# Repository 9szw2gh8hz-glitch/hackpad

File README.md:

<H1>Quel's Micropad

A small, customizable 5-key macropad with a rotary encoder, powered by the Seeed Studio XIAO RP2040-DIP.
Designed for simple shortcuts and macros.

<H1>Screenshots

<H1>BOM
  
1. Seeed XIAO RP2040-DIP
2. 5 Cherry MX Mechanical Switches
3. 5 1N4148 Diodes
4. EC11 Rotary Encoder
5. 4 M3x16mm screws

<H1>Firmware
This macropad can run two firmwares:

- QMK
- KMK

<H1>Assembly

1. Solder diodes
2. Solder MX switches
3. Insert and solder the XIAO RP2040-DIP
4. Solder the rotary encoder
5. Attach switches + keycaps
6. crew the case together
7. Flash firmware (QMK/KMK)

<H1>Usage

Use it for streaming macros, Photoshop tools, coding shortcuts, volume knob, or gaming functions
Encoder can control volume, scrolling, timeline scrubbing, etc.

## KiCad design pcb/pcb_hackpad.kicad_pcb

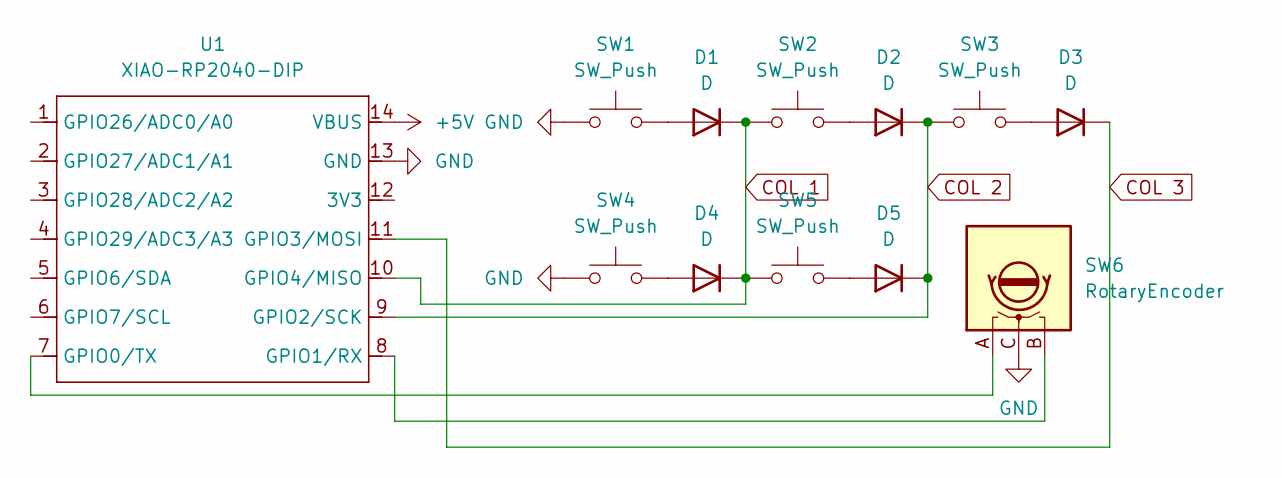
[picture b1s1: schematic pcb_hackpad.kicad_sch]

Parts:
D1, D2, D3, D4, D5: D; LED_PLCC-2_3.4x3.0mm_AK
SW1, SW2, SW3, SW4, SW5: SW_Push; SW_Cherry_MX_1.00u_PCB
SW6: RotaryEncoder; RotaryEncoder_Alps_EC11E_Vertical_H20mm_CircularMountingHol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
U1: XIAO-RP2040-DIP

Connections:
+5V: U1.14 (VBUS)
COL 1: D1.1 (K), D4.1 (K), SW2.1, SW5.1, U1.10 (GPIO4/MISO)
COL 2: D2.1 (K), D5.1 (K), SW3.1, U1.9 (GPIO2/SCK)
COL 3: D3.1 (K), U1.11 (GPIO3/MOSI)
GND: SW1.1, SW4.1, SW6.C, U1.13 (GND)
unnamed: D1.2 (A), SW1.2
unnamed: D2.2 (A), SW2.2
unnamed: D3.2 (A), SW3.2
unnamed: D4.2 (A), SW4.2
unnamed: D5.2 (A), SW5.2
unnamed: SW6.A, U1.7 (GPIO0/TX)
unnamed: SW6.B, U1.8 (GPIO1/RX)

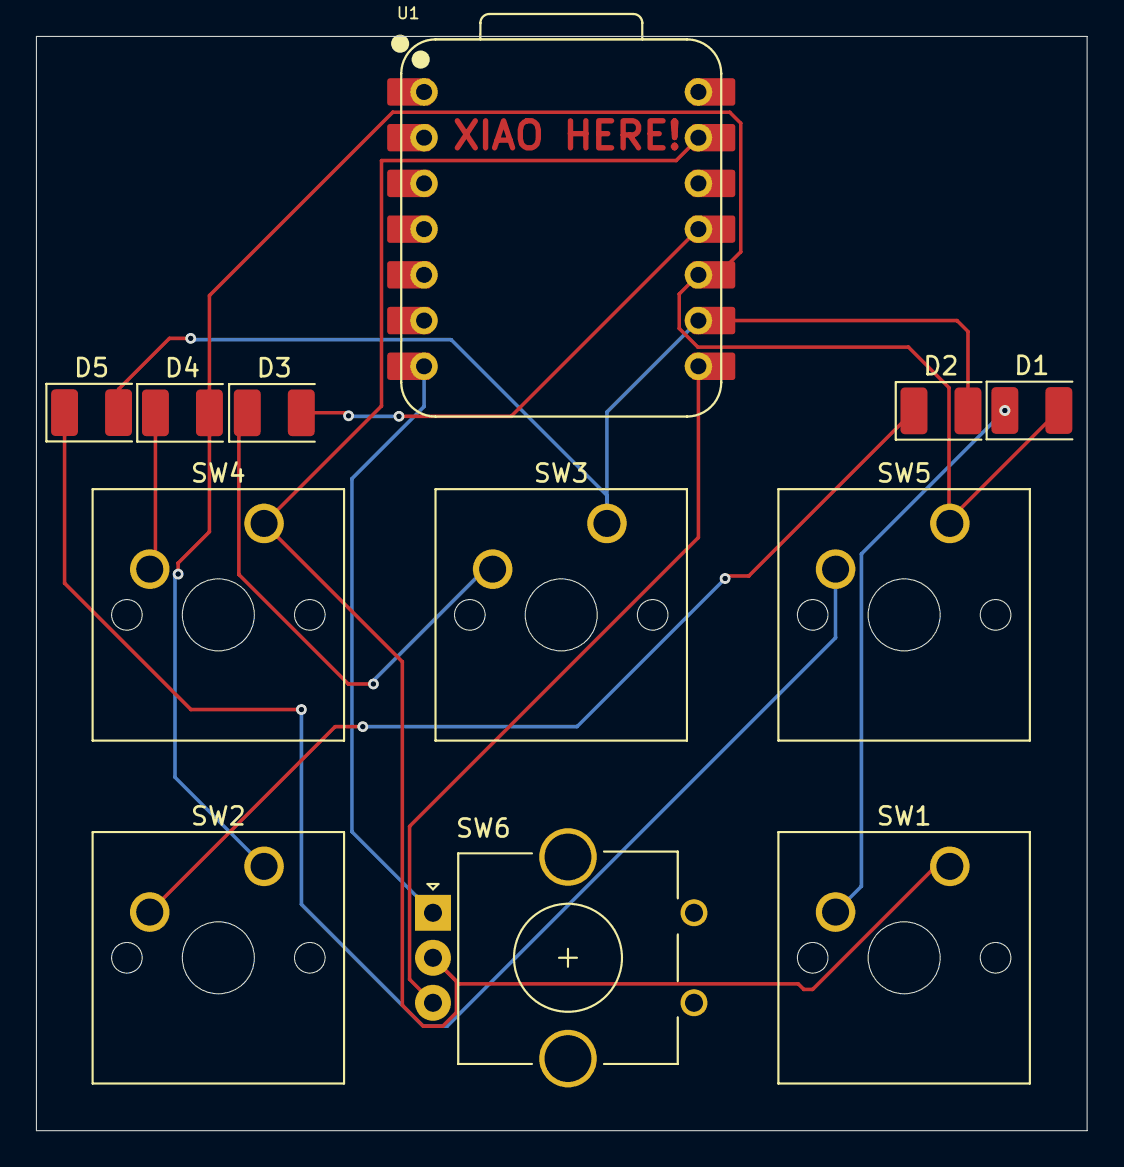
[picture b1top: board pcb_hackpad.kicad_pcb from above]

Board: 2 copper layers, 58.4 x 60.8 mm, 12 parts (0 on the bottom side), 11 nets.

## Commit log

2025-12-05 Create temp
2025-12-05 Add config.h for QMK firmware setup
    Add configuration for QMK firmware including matrix and encoder settings.
2025-12-05 Refactor README.md for improved formatting
    Updated formatting and structure of the README file.
